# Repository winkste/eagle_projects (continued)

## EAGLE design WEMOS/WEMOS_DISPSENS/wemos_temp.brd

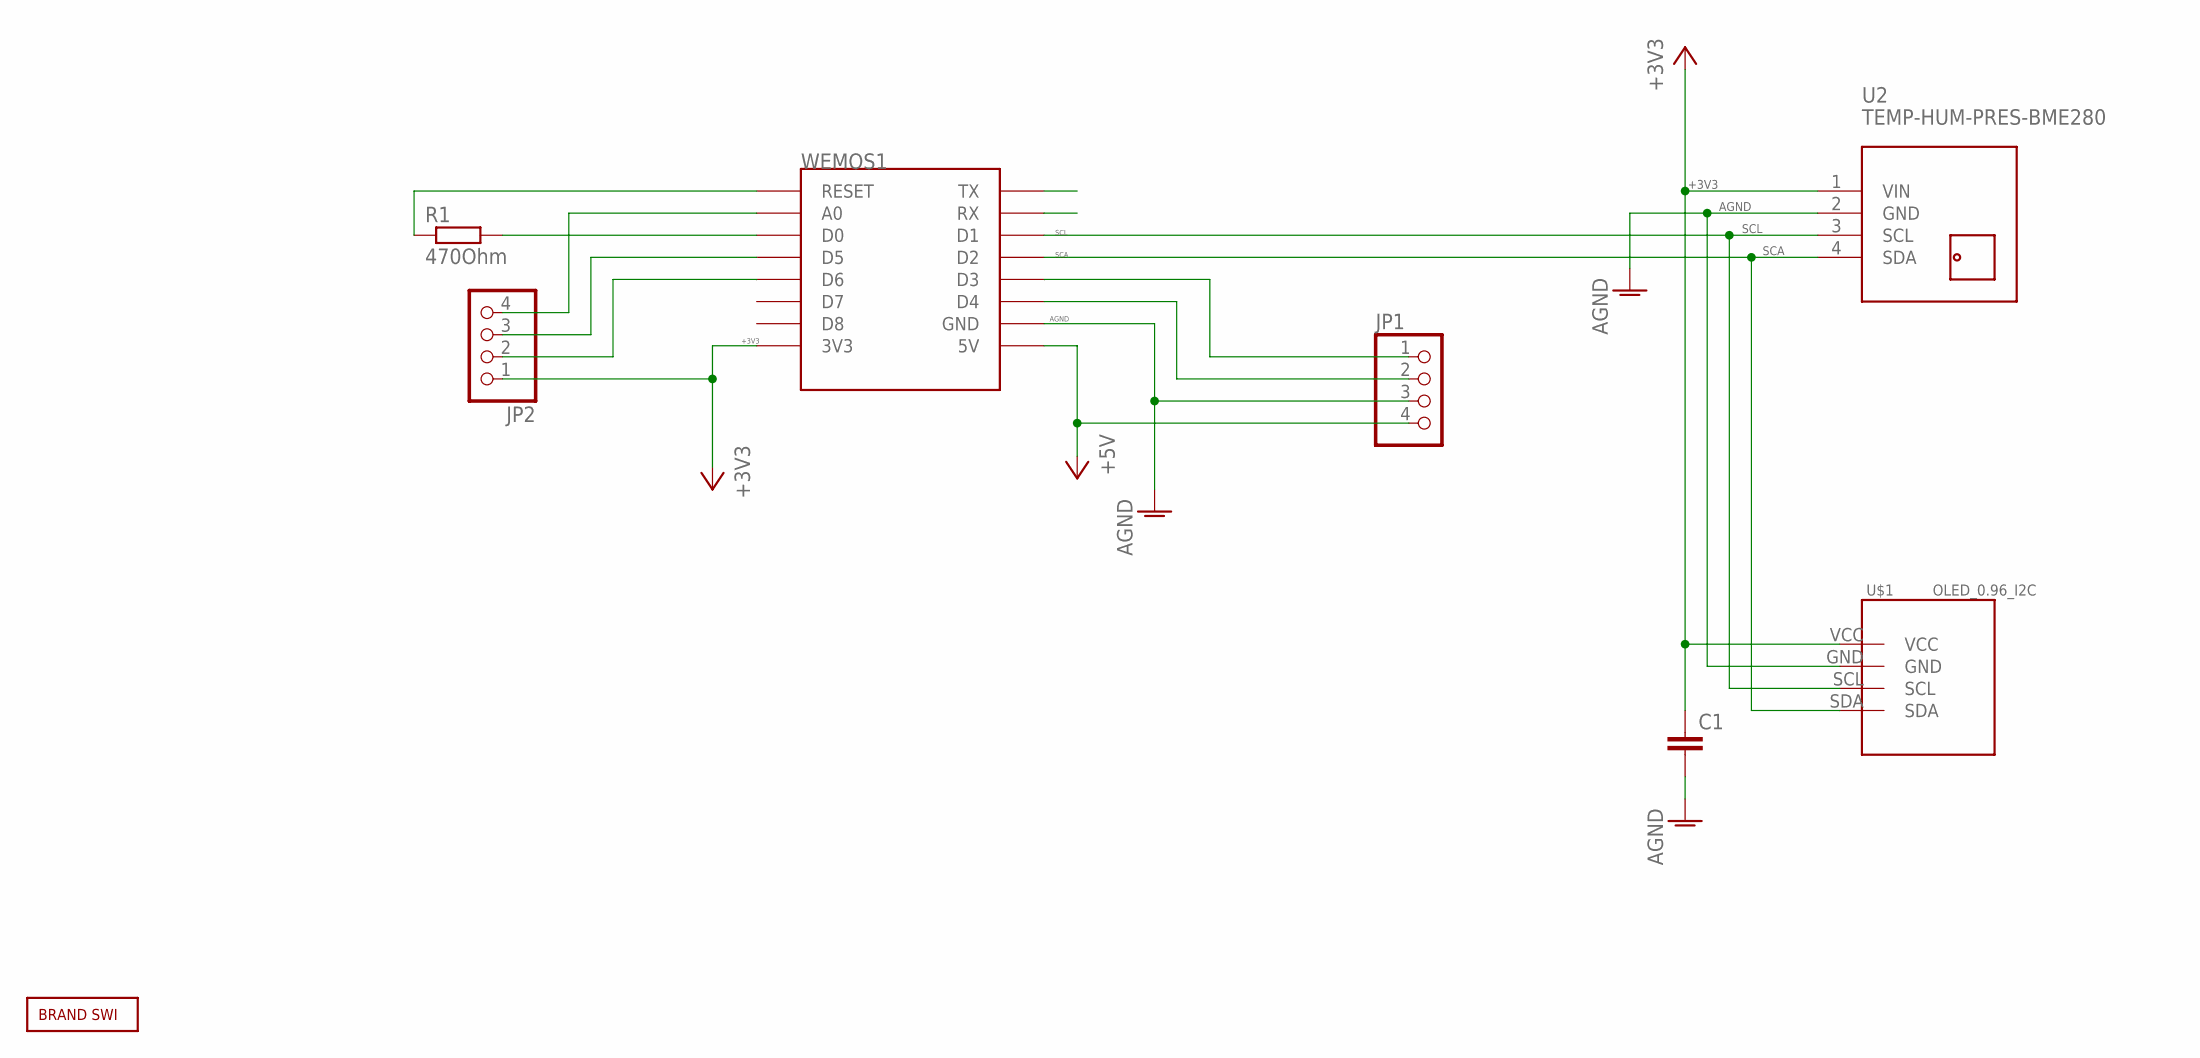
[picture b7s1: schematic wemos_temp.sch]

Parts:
C1: C-EUC1210; C1210
JP1, JP2: PINHD-1X4; 1X04
R1: 470Ohm; R0805
U2: TEMP-HUM-PRES-BME280
U$1: OLED_0.96_I2C
U$2: BRAND_SWI5X7; BRAND_SWI_5X7
WEMOS1: WEMOS-D1-MINI

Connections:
+3V3: C1.1, JP2.1, U2.1 (VIN), U$1.VCC, WEMOS1.3V3
+5V: JP1.4, WEMOS1.5V
AGND: C1.2, JP1.3, U2.2 (GND), U$1.GND, WEMOS1.GND
D4: JP1.2, WEMOS1.D4
unnamed: R1.1, WEMOS1.RESET
unnamed: R1.2, WEMOS1.D0
unnamed: JP1.1, WEMOS1.D3
unnamed: JP2.4, WEMOS1.A0
unnamed: JP2.3, WEMOS1.D5
unnamed: JP2.2, WEMOS1.D6
RX: WEMOS1.RX
SCA: U2.4 (SDA), U$1.SDA, WEMOS1.D2
SCL: U2.3 (SCL), U$1.SCL, WEMOS1.D1
TX: WEMOS1.TX

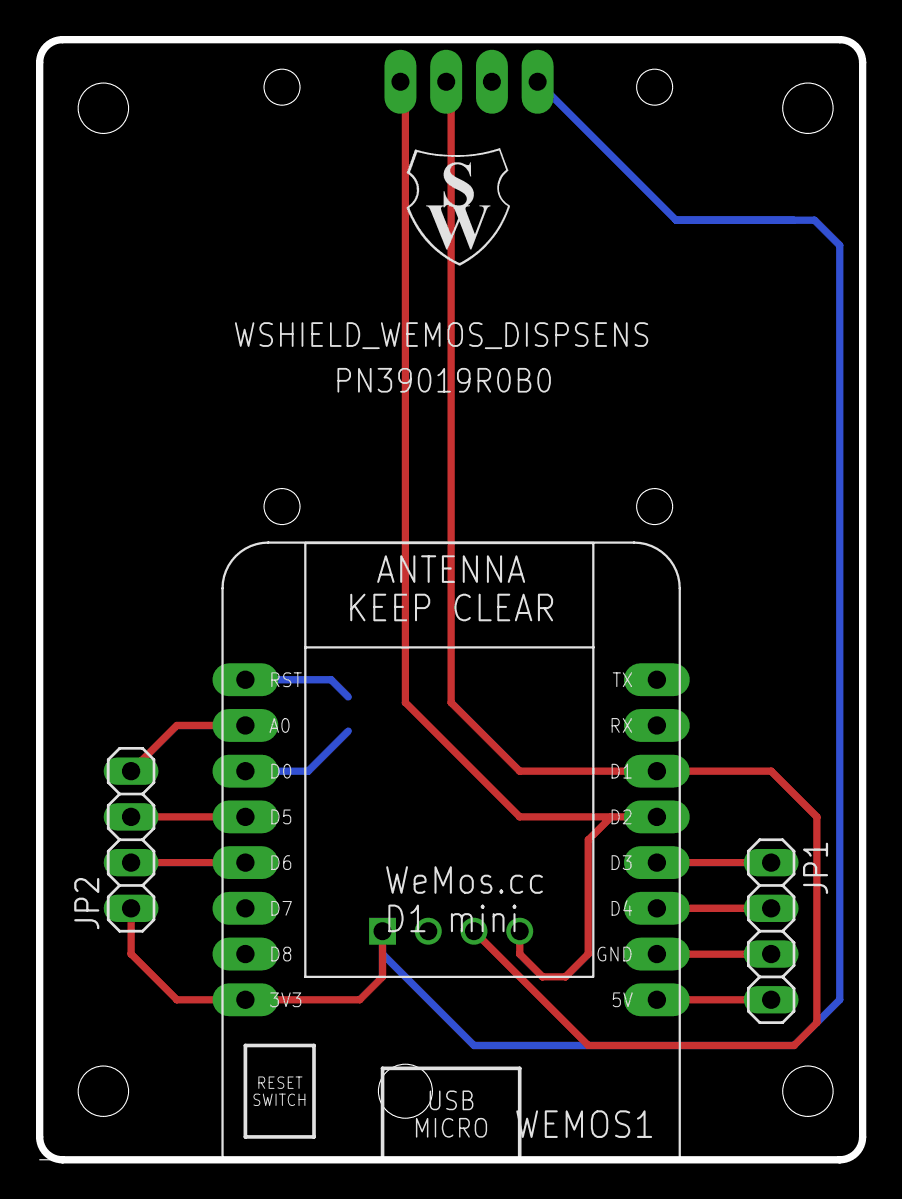
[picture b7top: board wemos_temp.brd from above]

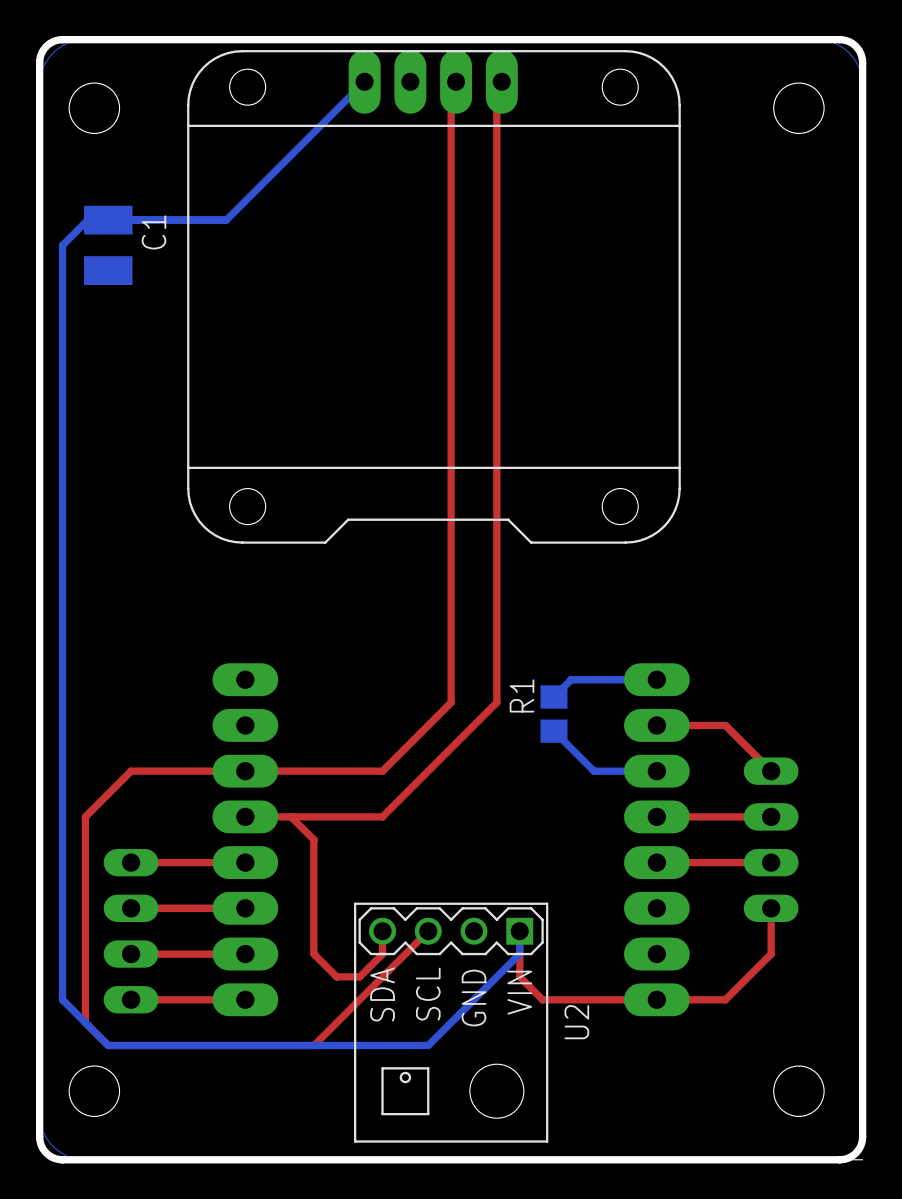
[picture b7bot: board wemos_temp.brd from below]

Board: 2 copper layers, 45.7 x 62.2 mm, 8 parts (4 on the bottom side), 12 nets.

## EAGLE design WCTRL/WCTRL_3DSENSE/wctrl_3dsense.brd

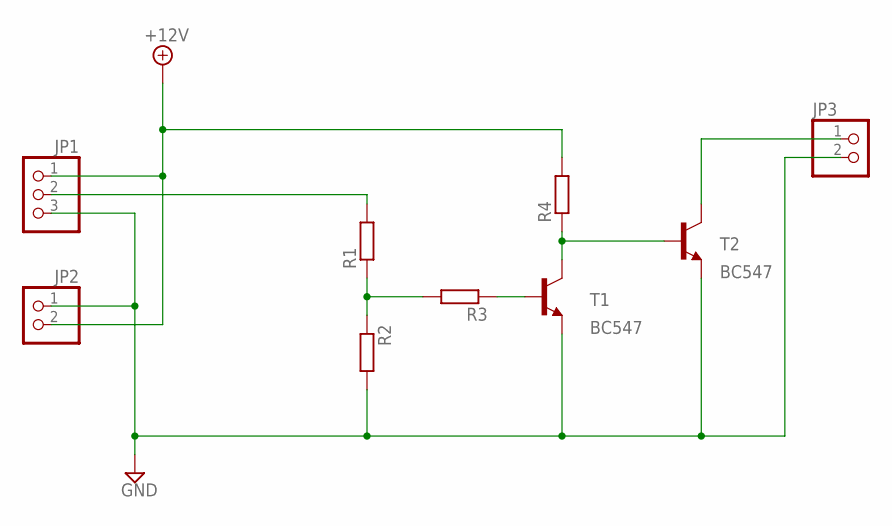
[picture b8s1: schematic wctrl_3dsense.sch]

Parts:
JP1: PINHD-1X3; 1X03
JP2, JP3: PINHD-1X2; 1X02
R1, R2, R3, R4: R-EU_0207/10; 0207/10
T1, T2: BC547; TO92

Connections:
+12V: JP1.1, JP2.2, R4.2
GND: JP1.3, JP2.1, JP3.2, R2.2, T1.1 (E), T2.1 (E)
unnamed: JP1.2, R1.2
unnamed: R1.1, R2.1, R3.2
unnamed: R3.1, T1.2 (B)
unnamed: JP3.1, T2.3 (C)
unnamed: R4.1, T1.3 (C), T2.2 (B)

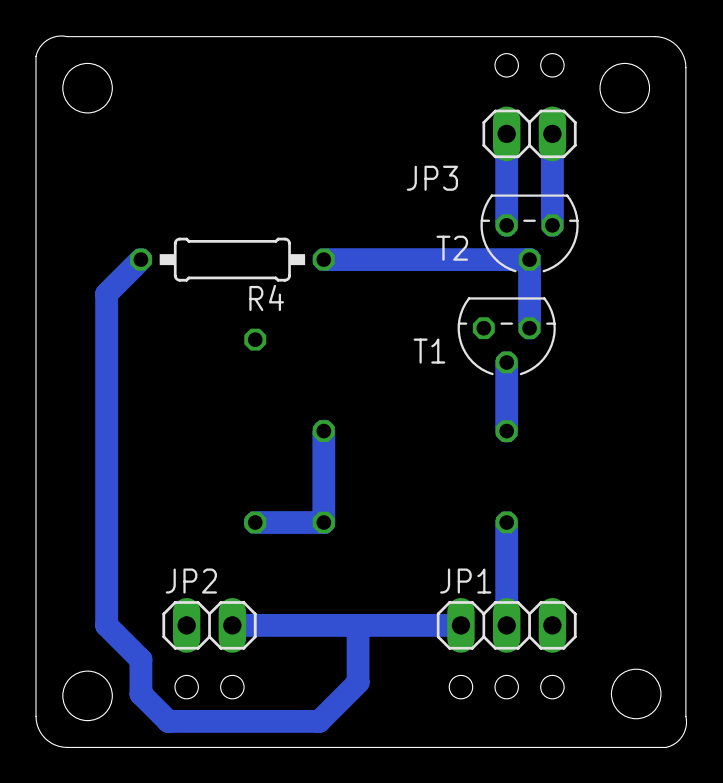
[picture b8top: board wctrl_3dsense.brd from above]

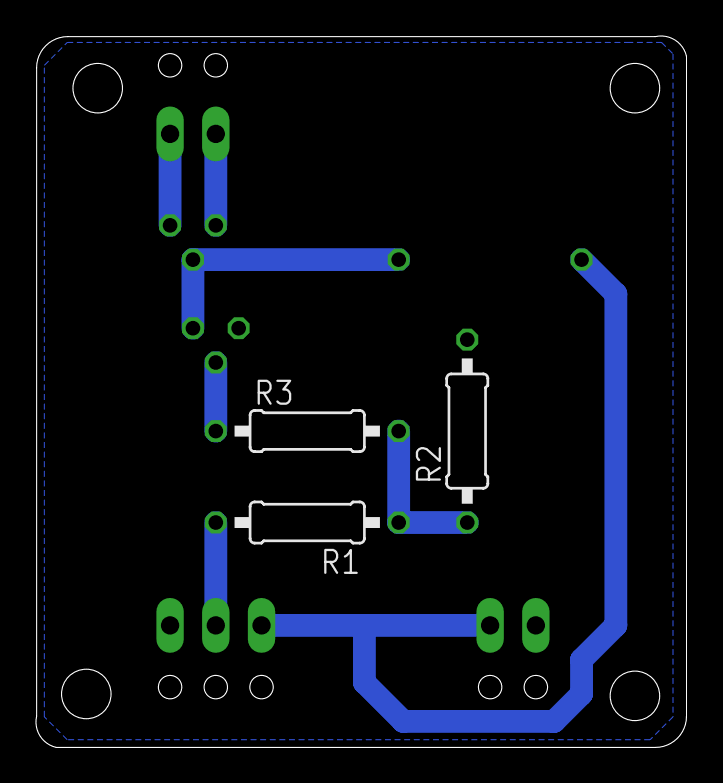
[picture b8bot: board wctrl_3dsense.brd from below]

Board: 2 copper layers, 36.1 x 39.5 mm, 9 parts (3 on the bottom side), 7 nets.

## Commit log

2018-03-21 initial import ATTiny projects
2018-03-22 initial import of all my eagle projects
2018-03-22 final attiny_batsense2 layout
2018-04-09 updated boards and wirings
2018-04-12 updated wiring
2018-06-03 reworked wemos gpio, reworked wiring for garden control
2018-07-03 reworked wiring to 2 wemos controller setup
    using 2 wemos controllers
2018-07-09 initial checkin of multi sense wiring
2020-03-17 test checkin
2020-03-17 integration checkin
2020-08-31 blink tutorial
2020-08-31 pinout documentation
2020-08-31 reworked structure
2020-09-04 updated wemos and diverse boards
2020-09-04 layout started
2020-09-09 final blink tutorial board
    changed to bottom layer connections
2020-09-09 shematic ready, started placing
2020-09-09 layout progress update
2020-09-15 modified for cnc manufacturing
2020-09-24 modified layout for manufacturing
2020-09-24 changed resistor footprint to 1206
2020-12-19 multi_Sense32 first batch ordered
2021-10-10 updated board design
